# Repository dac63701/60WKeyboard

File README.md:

# Custom Keyboard Project

A wireless, 60% layout, hot swappable, custom keyboard designed with an nRF52840 in Kicad. This keyboard is meant to be as efficient as possible for longer battery life.

## Criteria
- Wireless
- 60% Layout
- RGB Lighting
- Good Battery Life
- Cherry MX Switch Form Factor
- Hotswap Switches

## Materials
- [ ] PCBs ([JLCPCB](https://jlcpcb.com))
- [ ] Solder Stencil ([JLCPCB](https://jlcpcb.com))
- [x] Solder Paste ([Amazon](https://www.amazon.com/gp/product/B0BLSJQPR6/ref=ox_sc_act_title_7?smid=A1NSYQXYRWRLYY&psc=1))
- [x] Flux ([Amazon](https://www.amazon.com/gp/product/B08KJRCYRH/ref=ox_sc_act_title_8?smid=A2GPLZGUK8NBW5&psc=1))
- [x] Lead-Free Solder ([Amazon](https://www.amazon.com/gp/product/B07Q167J98/ref=ewc_pr_img_4?smid=A2SCLCWYE2XLX3&psc=1))
- [x] Solder Wick ([Amazon](https://www.amazon.com/gp/product/B094GZ6CPZ/ref=ox_sc_act_title_11?smid=ATC1HM24MD6HA&psc=1))
- [x] Solder Tip Tinner ([Amazon](https://www.amazon.com/gp/product/B00NS4J6BY/ref=ewc_pr_img_1?smid=A614WYM65K035&psc=1))
- [x] Switches ([Gateron Milky Yellows](https://www.amazon.com/gp/product/B0BBPD1W9W/ref=ox_sc_act_title_13?smid=A3L9NMSYTD5SO9&psc=1))
- [ ] Hot Swap Sockets ([Amazon](https://www.amazon.com/gp/product/B0B4W9YMGM/ref=ox_sc_act_title_14?smid=A1G6HFHDKP9H5J&psc=1))
- [ ] Stabilizers ([Amazon](https://www.amazon.com/gp/product/B0CN36LV22/ref=ox_sc_act_title_12?smid=A1G6HFHDKP9H5J&psc=1))
- [x] Keycaps (Aliexpress)
- [ ] Case (3d Printed)

## Electronic Components ([Digikey](https://www.digikey.com/))
- Main MCU - [nRF52840](https://www.nordicsemi.com/Products/nRF52840)
- PMIC - [nPM1300](https://www.nordicsemi.com/Products/nPM1300)
- RGB LEDs - [SK6812mini-e](https://www.aliexpress.us/item/3256809003632879.html?spm=a2g0o.order_list.order_list_main.5.75471802QNYOMN&gatewayAdapt=glo2usa)
- Supporting Components...

## Tools
- [x] Adjustable Temperature Soldering Iron ([8786D](https://www.amazon.com/gp/product/B0BXN5NXFQ/ref=ox_sc_act_title_6?smid=A1YPRZ9PDHRQA5&psc=1))
- [x] Hot Air Station ([8786D](https://www.amazon.com/gp/product/B0BXN5NXFQ/ref=ox_sc_act_title_6?smid=A1YPRZ9PDHRQA5&psc=1))
- [x] Hot Plate (Amazon)
- [x] Fume Extractor ([Kotto](https://www.amazon.com/gp/product/B07VWDN29F/ref=ox_sc_act_title_2?smid=A38V7SOCF2OM8H&psc=1))
- [x] Digital Microscope ([AD246S-M](https://www.amazon.com/gp/product/B09VPPS96M/ref=ox_sc_act_title_5?smid=A2YDP7W2SGBPL2&psc=1))
- [ ] Tweezers (Amazon)
- [ ] Helping Hands ([Amazon](https://www.amazon.com/gp/product/B0BHHVP467/ref=ox_sc_act_title_10?smid=A3FKADQL4BXVZ2&psc=1))
- [ ] Soldering Iron Brass Sponge ([Amazon](https://www.amazon.com/gp/product/B08FQBS97L/ref=ox_sc_act_title_9?smid=ATVPDKIKX0DER&psc=1))
- [x] 3d Printer

## Steps
1. [x] Select Components
2. [x] Design Schematic
3. [x] Design PCB
4. [ ] Order PCB and Stencil
5. [ ] Order Electronic Components
6. [x] Acquire the necessary tools
7. [ ] Assemble boards
8. [ ] Test and validate

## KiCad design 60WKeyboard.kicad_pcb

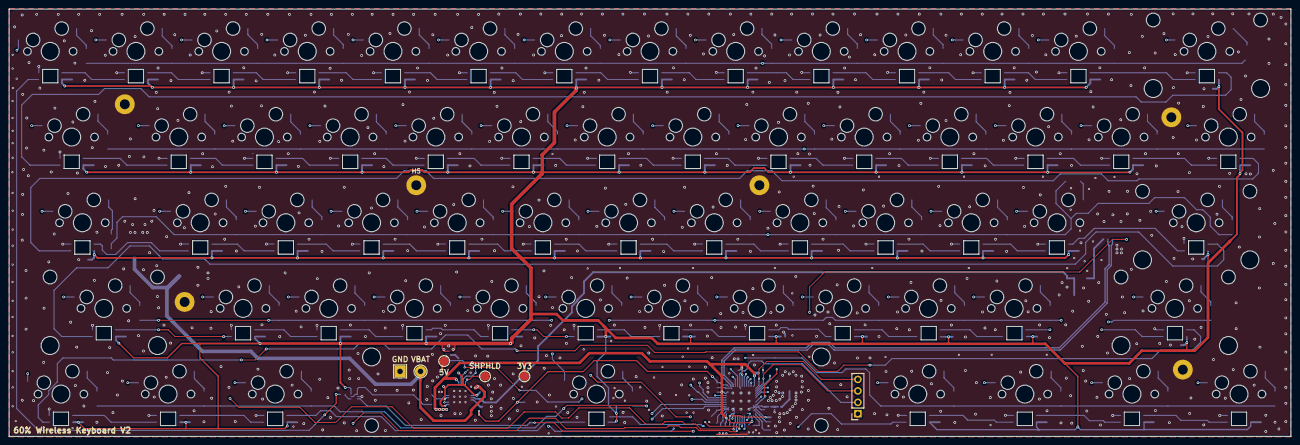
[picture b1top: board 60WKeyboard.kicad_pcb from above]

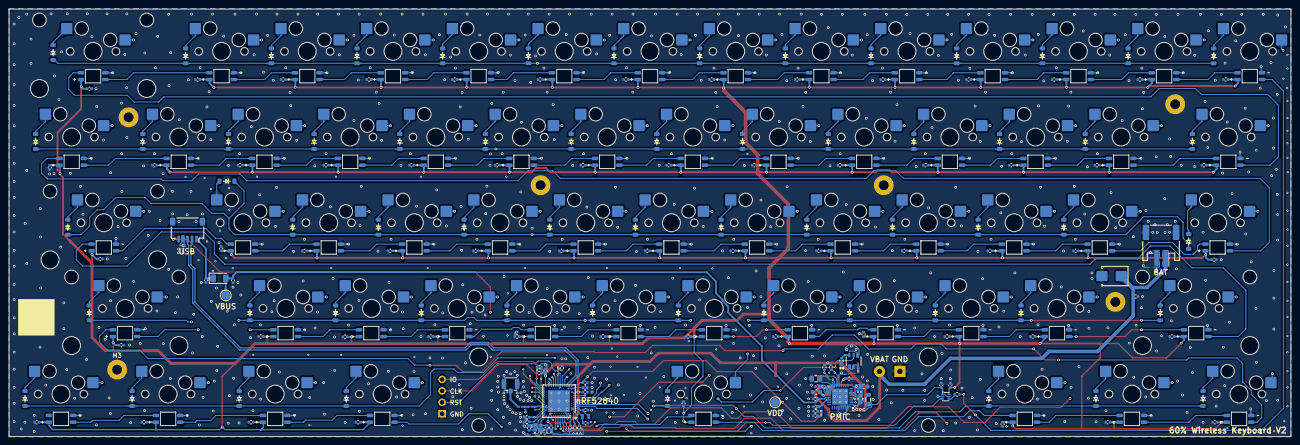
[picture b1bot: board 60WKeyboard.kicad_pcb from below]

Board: 4 copper layers, 285.0 x 95.0 mm, 310 parts (299 on the bottom side), 174 nets.

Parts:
3V3: USB_VBUS; TestPoint_Pad_D2.0mm
5V: 5V; TestPoint_Pad_D2.0mm
C1, C6, C8, C10, C13, C14, C30, C31, C32, C33, C34, C35, C36, C37, C38, C39, C40, C41, C42, C43, C44, C45, C46, C47, C48, C49, C50, C51, C52, C53, C54, C55, C56, C57, C58, C59, C60, C61, C62, C63, C64, C65, C66, C67, C68, C69, C70, C71, C72, C73, C74, C75, C76, C77, C78, C79, C80, C81, C82, C83, C84, C85, C86, C87, C88, C89, C90, C91, C92, C93: 100nF; C_0402_1005Metric
C2, C3, C5: 4.7uF; C_0402_1005Metric
C4, C11, C15: 1uF; C_0402_1005Metric
C7: DNP; C_0402_1005Metric
C9: 100pF; C_0402_1005Metric
C12, C17, C18, C19: 8pF; C_0402_1005Metric
C16: 2.2uF; C_0402_1005Metric
C20, C21, C22: 10uF; C_0603_1608Metric
C23, C24, C25: 3.3uF; C_0402_1005Metric
C26: 1pF; C_0201_0603Metric
C27, C29: 0.1uF; C_0402_1005Metric
C28: 1.2pF; C_0201_0603Metric
D1: D_TVS; D_SMB
D2, D3, D4, D5, D6, D7, D8, D9, D10, D11, D12, D13, D14, D15, D16, D17, D18, D19, D20, D21, D22, D23, D24, D25, D26, D27, D28, D29, D30, D31, D32, D33, D34, D35, D36, D37, D38, D39, D40, D41, D42, D43, D44, D45, D46, D47, D48, D49, D50, D51, D52, D53, D54, D55, D56, D57, D58, D59, D60, D61, D62: Diode; Diode_SOD-123
FB1: 300R; D_1206_3216Metric
GND: GND; TestPoint_THTPad_2.5x2.5mm_Drill1.2mm
H1, H2, H3, H4, H5, H6: MountingHole_Pad; MountingHole_2.2mm_M2_Pad
J1: Conn_02x01_MountingPin; JST_PH_S2B-PH-SM4-TB_1x02-1MP_P2.00mm_Horizontal
J2: Conn_01x04_Socket; PinSocket_1x04_P2.54mm_Vertical
J4: Conn_01x05_MountingPin; JST_SH_SM05B-SRSS-TB_1x05-1MP_P1.00mm_Horizontal
J5: Conn_Coaxial; U.FL_Hirose_U.FL-R-SMT-1_Vertical
L1: 2.2uH; L_0805_2012Metric
L2: 4.7nH; L_0201_0603Metric
L3: 2.2nH; L_0201_0603Metric
LED1, LED2, LED3, LED4, LED5, LED6, LED7, LED8, LED9, LED10, LED11, LED12, LED13, LED14, LED15, LED16, LED17, LED18, LED19, LED20, LED21, LED22, LED23, LED24, LED25, LED26, LED27, LED28, LED29, LED30, LED31, LED32, LED33, LED34, LED35, LED36, LED37, LED38, LED39, LED40, LED41, LED42, LED43, LED44, LED45, LED46, LED47, LED48, LED49, LED50, LED51, LED52, LED53, LED54, LED55, LED56, LED57, LED58, LED59, LED60, LED61: SK6812-E; LED_SK6812-E
MOSFET1: SI3865DDV-T1-GE3; TSOP6_MO-193C_VIS
PMIC: NPM1300-QEAA-R; QFN50P500X500X90-33N
R1: 250k; R_0805_2012Metric
R2, R3, R6: 10k; R_0402_1005Metric
R5: 300; R_0402_1005Metric
R7: 100k; R_0402_1005Metric
S1, S6, S7, S8, S10, S11, S12, S13, S15, S16, S17, S18, S19, S20, S21, S22, S23, S24, S25, S26, S27, S28, S29, S30, S32, S33, S34, S35, S36, S37, S38, S39, S40, S41, S42, S43, S44, S45, S46, S47, S49, S50, S51, S52, S54, S55: Keyswitch; MX-Hotswap-1U
S2, S58: Keyswitch; MX-Hotswap-1.5U
S3: Keyswitch; MX-Hotswap-1.75U
S4, S59: Keyswitch; MX-Hotswap-2.25U
S5, S9, S14, S48, S53, S56, S61: Keyswitch; MX-Hotswap-1.25U
S31: Keyswitch; MX-Hotswap-6.25U-ReversedStabilizers
S57: Keyswitch; MX-Hotswap-2U
S60: Keyswitch; MX-Hotswap-2.75U
SHPHLD: VBUSOUT; TestPoint_Pad_D2.0mm
U1: nRF52840; Nordic_AQFN-73-1EP_7x7mm_P0.5mm
U2: TXB0101DRL; SOT-563
VBAT: +BATT; TestPoint_THTPad_D2.5mm_Drill1.2mm
VBUS: USB_VBUS; TestPoint_Pad_D2.0mm
VDD: VBUSOUT; TestPoint_Pad_D2.0mm
Y1: ABM11W-32.0000MHZ-7-D1X-T3; ABM11W300000MHZ4B1UT3
Y2: ECS-.327-7-12-TR; XTAL_ECS-.327-7-12-TR

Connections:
+3V3: 3V3.1 (1_1), C2.1, C4.2, C6.1, C8.1, C10.1, C14.1, C22.1, C86.2, L1.1, PMIC.12 (VDDIO), PMIC.32 (VOUT2), R2.2, R3.2, R6.1, U1.A22 (VDD), U1.AD14 (VDD), U1.AD23 (VDD), U1.B1 (VDD), U1.W1 (VDD), U1.Y2 (VDDH), U2.1 (V_{CCA}), U2.5 (OE)
+5V: 5V.1 (1_1), C20.1, C21.1, C30.1, C31.1, C33.1, C34.1, C35.1, C36.1, C37.1, C38.1, C39.1, C40.1, C41.1, C42.1, C43.1, C44.1, C45.1, C46.1, C47.1, C48.1, C49.1, C50.1, C51.1, C52.1, C53.1, C54.1, C55.1, C56.1, C57.1, C58.1, C59.1, C60.1, C61.1, C62.1, C63.1, C64.1, C65.1, C66.1, C67.1, C68.1, C69.1, C70.1, C71.1, C72.1, C73.1, C74.1, C75.1, C76.1, C77.1, C78.1, C79.1, C80.1, C81.1, C82.1, C83.1, C84.1, C85.1, C87.1, C88.1, C89.1, C90.1, C91.1, C92.1, C93.1, LED1.1 (VDD), LED2.1 (VDD), LED3.1 (VDD), LED4.1 (VDD), LED5.1 (VDD), LED6.1 (VDD), LED7.1 (VDD), LED8.1 (VDD), LED9.1 (VDD), LED10.1 (VDD), LED11.1 (VDD), LED12.1 (VDD), LED13.1 (VDD), LED14.1 (VDD), LED15.1 (VDD), LED16.1 (VDD), LED17.1 (VDD), LED18.1 (VDD), LED19.1 (VDD), LED20.1 (VDD), LED21.1 (VDD), LED22.1 (VDD), LED23.1 (VDD), LED24.1 (VDD), LED25.1 (VDD), LED26.1 (VDD), LED27.1 (VDD), LED28.1 (VDD), LED29.1 (VDD), LED30.1 (VDD), LED31.1 (VDD), LED32.1 (VDD), LED33.1 (VDD), LED34.1 (VDD), LED35.1 (VDD), LED36.1 (VDD), LED37.1 (VDD), LED38.1 (VDD), LED39.1 (VDD), LED40.1 (VDD), LED41.1 (VDD), LED42.1 (VDD), LED43.1 (VDD), LED44.1 (VDD), LED45.1 (VDD), LED46.1 (VDD), LED47.1 (VDD), LED48.1 (VDD), LED49.1 (VDD), LED50.1 (VDD), LED51.1 (VDD), LED52.1 (VDD), LED53.1 (VDD), LED54.1 (VDD), LED55.1 (VDD), LED56.1 (VDD), LED57.1 (VDD), LED58.1 (VDD), LED59.1 (VDD), LED60.1 (VDD), LED61.1 (VDD), MOSFET1.1 (R2), MOSFET1.2 (D2), MOSFET1.3 (D2), MOSFET1.4 (S2), PMIC.1 (VOUT1), PMIC.4 (PVDD), PMIC.20 (VSYS), R7.2, U2.6 (V_{CCB})
+BATT: C13.1, C16.2, D1.1 (A1), J1.1, PMIC.19 (VBAT), VBAT.1 (1_1)
/ANT: C26.1, L2.1, U1.H23 (ANT)
/COL_0: S1.1, S2.1, S3.1, S4.1, S5.1, U1.A10 (AIN5/P0.29)
/COL_1: S6.1, S7.1, S8.1, S9.1, U1.A8 (AIN7/P0.31)
/COL_2: S10.1, S11.1, S12.1, S13.1, S14.1, U1.A14 (P1.15)
/COL_3: S15.1, S16.1, S17.1, S18.1, U1.A12 (AIN0/P0.02)
/COL_4: S19.1, S20.1, S21.1, S22.1, U1.A20 (P1.10)
/COL_5: S23.1, S24.1, S25.1, S26.1, U1.B19 (P1.11)
/COL_6: S27.1, S28.1, S29.1, S30.1, S31.1, U1.U1 (TRACEDATA1/P0.12)
/COL_7: S32.1, S33.1, S34.1, S35.1, U1.N1 (P0.08)
/COL_8: S36.1, S37.1, S38.1, S39.1, U1.R1 (TRACEDATA3/P1.09)
/COL_9: S40.1, S41.1, S42.1, S43.1, U1.AD22 (TRACEDATA0/P1.00)
/COL_10: S44.1, S45.1, S46.1, S47.1, S48.1, U1.U24 (P1.04)
/COL_11: S49.1, S50.1, S51.1, S52.1, S53.1, U1.W24 (P1.02)
/COL_12: S54.1, S55.1, S56.1, U1.J24 (NFC2/P0.10)
/COL_13: S57.1, S58.1, S59.1, S60.1, S61.1, U1.R24 (P1.06)
/C_VBUS: C27.1, FB1.1, J4.1
/DEC 1: C1.2, U1.C1 (DEC1)
/DEC 3: C9.1, U1.D23 (DEC3)
/DEC 4 6: C7.1, C11.2, U1.B5 (DEC4), U1.E24 (DEC6)
/DECUSB: C5.1, U1.AC5 (DECUSB)
/LEDs/RGB_DIN_5V: LED1.4 (DIN), R5.1
/PWR_SW: C32.2, J4.5, R6.2, U1.L24 (NFC1/P0.09)
/RESET: J2.2, U1.AC13 (P0.18/~RESET), U1.AD12 (P0.17)
/RF: J5.1 (In), L3.2
/RGB_DIN_3V3: U1.A16 (P1.13), U2.3 (A)
/RGB_POWER: MOSFET1.5 (ON/OFF), U1.L1 (P0.06)
/ROW_0: D2.1 (K), D7.1 (K), D11.1 (K), D16.1 (K), D20.1 (K), D24.1 (K), D28.1 (K), D33.1 (K), D37.1 (K), D41.1 (K), D45.1 (K), D50.1 (K), D55.1 (K), D58.1 (K), U1.AD20 (P0.24)
/ROW_1: D3.1 (K), D8.1 (K), D12.1 (K), D17.1 (K), D21.1 (K), D25.1 (K), D29.1 (K), D34.1 (K), D38.1 (K), D42.1 (K), D46.1 (K), D51.1 (K), D56.1 (K), D59.1 (K), U1.AD18 (P0.22)
/ROW_2: D4.1 (K), D9.1 (K), D13.1 (K), D18.1 (K), D22.1 (K), D26.1 (K), D30.1 (K), D35.1 (K), D39.1 (K), D43.1 (K), D47.1 (K), D52.1 (K), D60.1 (K), U1.AD16 (P0.20)
/ROW_3: D5.1 (K), D14.1 (K), D19.1 (K), D23.1 (K), D27.1 (K), D31.1 (K), D36.1 (K), D40.1 (K), D44.1 (K), D48.1 (K), D53.1 (K), D61.1 (K), U1.AD10 (P0.15)
/ROW_4: D6.1 (K), D10.1 (K), D15.1 (K), D32.1 (K), D49.1 (K), D54.1 (K), D57.1 (K), D62.1 (K), U1.AD8 (P0.13)
/SCL: PMIC.14 (SCL), R2.1, U1.G1 (P0.26)
/SDA: PMIC.13 (SDA), R3.1, U1.J1 (AIN2/P0.04)
/SHPHLD: PMIC.15 (SHPHLD), SHPHLD.1 (1_1)
/SWDCLK: J2.3, U1.AA24 (SWDCLK)
/SWDIO: J2.4, U1.AC24 (SWDIO)
/USB_DN: J4.2, U1.AD4 (D-)
/USB_DP: J4.3, U1.AD6 (D+)
/XC1: C12.1, U1.B24 (XC1), Y1.1 (X1)
/XC2: C17.1, U1.A23 (XC2), Y1.3 (X2)
/XL1: C18.2, U1.D2 (XL1/P0.00), Y2.1
/XL2: C19.2, U1.F2 (XL2/P0.01), Y2.2
GND: C1.1, C2.2, C3.2, C4.1, C5.2, C6.2, C7.2, C8.2, C9.2, C10.2, C11.1, C12.2, C13.2, C14.2, C15.2, C16.1, C17.2, C18.1, C19.1, C20.2, C21.2, C22.2, C23.2, C24.2, C25.2, C26.2, C27.2, C28.2, C29.2, C30.2, C31.2, C32.1, C33.2, C34.2, C35.2, C36.2, C37.2, C38.2, C39.2, C40.2, C41.2, C42.2, C43.2, C44.2, C45.2, C46.2, C47.2, C48.2, C49.2, C50.2, C51.2, C52.2, C53.2, C54.2, C55.2, C56.2, C57.2, C58.2, C59.2, C60.2, C61.2, C62.2, C63.2, C64.2, C65.2, C66.2, C67.2, C68.2, C69.2, C70.2, C71.2, C72.2, C73.2, C74.2, C75.2, C76.2, C77.2, C78.2, C79.2, C80.2, C81.2, C82.2, C83.2, C84.2, C85.2, C86.1, C87.2, C88.2, C89.2, C90.2, C91.2, C92.2, C93.2, D1.2 (A2), GND.1 (1_1), H1.1 (1_1), H2.1 (1_1), H3.1 (1_1), H4.1 (1_1), H5.1 (1_1), H6.1 (1_1), J1.2, J1.MP (MountPin), J2.1, J4.4, J4.MP (MountPin), J5.2 (Ext), LED1.3 (GND), LED2.3 (GND), LED3.3 (GND), LED4.3 (GND), LED5.3 (GND), LED6.3 (GND), LED7.3 (GND), LED8.3 (GND), LED9.3 (GND), LED10.3 (GND), LED11.3 (GND), LED12.3 (GND), LED13.3 (GND), LED14.3 (GND), LED15.3 (GND), LED16.3 (GND), LED17.3 (GND), LED18.3 (GND), LED19.3 (GND), LED20.3 (GND), LED21.3 (GND), LED22.3 (GND), LED23.3 (GND), LED24.3 (GND), LED25.3 (GND), LED26.3 (GND), LED27.3 (GND), LED28.3 (GND), LED29.3 (GND), LED30.3 (GND), LED31.3 (GND), LED32.3 (GND), LED33.3 (GND), LED34.3 (GND), LED35.3 (GND), LED36.3 (GND), LED37.3 (GND), LED38.3 (GND), LED39.3 (GND), LED40.3 (GND), LED41.3 (GND), LED42.3 (GND), LED43.3 (GND), LED44.3 (GND), LED45.3 (GND), LED46.3 (GND), LED47.3 (GND), LED48.3 (GND), LED49.3 (GND), LED50.3 (GND), LED51.3 (GND), LED52.3 (GND), LED53.3 (GND), LED54.3 (GND), LED55.3 (GND), LED56.3 (GND), LED57.3 (GND), LED58.3 (GND), LED59.3 (GND), LED60.3 (GND), LED61.3 (GND), PMIC.2 (PVSS1), PMIC.6 (PVSS2), PMIC.17 (VSET1), PMIC.18 (NTC), PMIC.28 (LSIN1/VINLDO1), PMIC.29 (LSOUT1/VOUTLDO1), PMIC.30 (LSIN2/VINLDO2), PMIC.31 (LSOUT2/VOUTLDO2), PMIC.33 (AVSS), R1.1, U1.B7 (VSS), U1.EP (VSS), U1.F23 (VSS_PA), U2.2 (GND), Y1.2 (GND_1), Y1.4 (GND_2)
unnamed: C28.1, L2.2, L3.1
unnamed: D2.2 (A), S1.2
unnamed: D3.2 (A), S2.2
unnamed: D4.2 (A), S3.2
unnamed: D5.2 (A), S4.2
unnamed: D6.2 (A), S5.2
unnamed: D7.2 (A), S6.2
unnamed: D8.2 (A), S7.2
unnamed: D9.2 (A), S8.2
unnamed: D10.2 (A), S9.2
unnamed: D11.2 (A), S10.2
unnamed: D12.2 (A), S11.2
unnamed: D13.2 (A), S12.2
unnamed: D14.2 (A), S13.2
unnamed: D15.2 (A), S14.2
unnamed: D16.2 (A), S15.2
unnamed: D17.2 (A), S16.2
unnamed: D18.2 (A), S17.2
unnamed: D19.2 (A), S18.2
unnamed: D20.2 (A), S19.2
unnamed: D21.2 (A), S20.2
unnamed: D22.2 (A), S21.2
unnamed: D23.2 (A), S22.2
unnamed: D24.2 (A), S23.2
unnamed: D25.2 (A), S24.2
unnamed: D26.2 (A), S25.2
unnamed: D27.2 (A), S26.2
unnamed: D28.2 (A), S27.2
unnamed: D29.2 (A), S28.2
unnamed: D30.2 (A), S29.2
unnamed: D31.2 (A), S30.2
unnamed: D32.2 (A), S31.2
unnamed: D33.2 (A), S32.2
unnamed: D34.2 (A), S33.2
unnamed: D35.2 (A), S34.2
unnamed: D36.2 (A), S35.2
unnamed: D37.2 (A), S36.2
unnamed: D38.2 (A), S37.2
unnamed: D39.2 (A), S38.2
unnamed: D40.2 (A), S39.2
unnamed: D41.2 (A), S40.2
unnamed: D42.2 (A), S41.2
unnamed: D43.2 (A), S42.2
unnamed: D44.2 (A), S43.2
unnamed: D45.2 (A), S44.2
unnamed: D46.2 (A), S45.2
unnamed: D47.2 (A), S46.2
unnamed: D48.2 (A), S47.2
unnamed: D49.2 (A), S48.2
unnamed: D50.2 (A), S49.2
unnamed: D51.2 (A), S50.2
unnamed: D52.2 (A), S51.2
unnamed: D53.2 (A), S52.2
unnamed: D54.2 (A), S53.2
unnamed: D55.2 (A), S54.2
unnamed: D56.2 (A), S55.2
unnamed: D57.2 (A), S56.2
unnamed: D58.2 (A), S57.2
unnamed: D59.2 (A), S58.2
unnamed: D60.2 (A), S59.2
unnamed: D61.2 (A), S60.2
unnamed: D62.2 (A), S61.2
unnamed: LED1.2 (DOUT), LED6.4 (DIN)
unnamed: LED2.4 (DIN), LED60.2 (DOUT)
unnamed: LED2.2 (DOUT), LED7.4 (DIN)
unnamed: LED3.4 (DIN), LED61.2 (DOUT)
unnamed: LED3.2 (DOUT), LED8.4 (DIN)
unnamed: LED4.4 (DIN), LED59.2 (DOUT)
unnamed: LED4.2 (DOUT), LED9.4 (DIN)
unnamed: LED5.4 (DIN), LED56.2 (DOUT)
unnamed: LED5.2 (DOUT), LED10.4 (DIN)
unnamed: LED10.2 (DOUT), LED15.4 (DIN)
unnamed: LED6.2 (DOUT), LED11.4 (DIN)
unnamed: LED11.2 (DOUT), LED16.4 (DIN)
unnamed: LED7.2 (DOUT), LED12.4 (DIN)
unnamed: LED12.2 (DOUT), LED17.4 (DIN)
unnamed: LED8.2 (DOUT), LED13.4 (DIN)
unnamed: LED13.2 (DOUT), LED18.4 (DIN)
unnamed: LED9.2 (DOUT), LED14.4 (DIN)
unnamed: LED14.2 (DOUT), LED19.4 (DIN)
unnamed: LED15.2 (DOUT), LED20.4 (DIN)
unnamed: LED16.2 (DOUT), LED21.4 (DIN)
unnamed: LED17.2 (DOUT), LED22.4 (DIN)
unnamed: LED18.2 (DOUT), LED23.4 (DIN)
unnamed: LED19.2 (DOUT), LED24.4 (DIN)
unnamed: LED20.2 (DOUT), LED25.4 (DIN)
unnamed: LED21.2 (DOUT), LED26.4 (DIN)
unnamed: LED22.2 (DOUT), LED27.4 (DIN)
unnamed: LED23.2 (DOUT), LED28.4 (DIN)
unnamed: LED24.2 (DOUT), LED29.4 (DIN)
unnamed: LED25.2 (DOUT), LED30.4 (DIN)
unnamed: LED26.2 (DOUT), LED31.4 (DIN)
unnamed: LED27.2 (DOUT), LED32.4 (DIN)
unnamed: LED28.2 (DOUT), LED33.4 (DIN)
unnamed: LED29.2 (DOUT), LED34.4 (DIN)
unnamed: LED30.2 (DOUT), LED35.4 (DIN)
unnamed: LED31.2 (DOUT), LED36.4 (DIN)
unnamed: LED32.2 (DOUT), LED37.4 (DIN)
unnamed: LED33.2 (DOUT), LED38.4 (DIN)
unnamed: LED34.2 (DOUT), LED39.4 (DIN)
unnamed: LED35.2 (DOUT), LED40.4 (DIN)
unnamed: LED36.2 (DOUT), LED41.4 (DIN)
unnamed: LED37.2 (DOUT), LED42.4 (DIN)
unnamed: LED38.2 (DOUT), LED43.4 (DIN)
unnamed: LED39.2 (DOUT), LED44.4 (DIN)
unnamed: LED41.2 (DOUT), LED45.4 (DIN)
unnamed: LED42.2 (DOUT), LED46.4 (DIN)
unnamed: LED43.2 (DOUT), LED47.4 (DIN)
unnamed: LED44.2 (DOUT), LED48.4 (DIN)
unnamed: LED45.2 (DOUT), LED49.4 (DIN)
unnamed: LED46.2 (DOUT), LED50.4 (DIN)
unnamed: LED47.2 (DOUT), LED51.4 (DIN)
unnamed: LED48.2 (DOUT), LED52.4 (DIN)
unnamed: LED49.2 (DOUT), LED53.4 (DIN)
unnamed: LED50.2 (DOUT), LED54.4 (DIN)
unnamed: LED51.2 (DOUT), LED55.4 (DIN)
unnamed: LED52.2 (DOUT), LED56.4 (DIN)
unnamed: LED53.2 (DOUT), LED57.4 (DIN)
unnamed: LED54.2 (DOUT), LED58.4 (DIN)
unnamed: LED55.2 (DOUT), LED59.4 (DIN)
unnamed: LED57.2 (DOUT), LED60.4 (DIN)
unnamed: LED58.2 (DOUT), LED61.4 (DIN)
unnamed: MOSFET1.6 (R1,C1), R7.1
unnamed: L1.2, PMIC.5 (SW2)
unnamed: PMIC.16 (VSET2), R1.2
unnamed: R5.2, U2.4 (B)
VBUS: C15.1, C29.1, FB1.2, PMIC.21 (VBUS), VBUS.1 (1_1)
VDD: C3.1, C23.1, C24.1, C25.1, PMIC.22 (VBUSOUT), U1.AD2 (VBUS), VDD.1 (1_1)

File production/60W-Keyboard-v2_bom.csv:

Designator,Footprint,Quantity,Value,LCSC Part #
"3V3, VBUS",TestPoint_Pad_D2.0mm,2,USB_VBUS,
5V,TestPoint_Pad_D2.0mm,1,5V,
"C1, C10, C13, C14, C30, C31, C32, C33, C34, C35, C36, C37, C38, C39, C40, C41, C42, C43, C44, C45, C46, C47, C48, C49, C50, C51, C52, C53, C54, C55, C56, C57, C58, C59, C6, C60, C61, C62, C63, C64, C65, C66, C67, C68, C69, C70, C71, C72, C73, C74, C75, C76, C77, C78, C79, C8, C80, C81, C82, C83, C84, C85, C86, C87, C88, C89, C90, C91, C92, C93",0402,70,100nF,
"C11, C15, C4",0402,3,1uF,
"C12, C17, C18, C19",0402,4,8pF,
C16,0402,1,2.2uF,
"C2, C3, C5",0402,3,4.7uF,
"C20, C21, C22",0603,3,10uF,
"C23, C24, C25",0402,3,3.3uF,
C26,0201,1,1pF,
"C27, C29",0402,2,0.1uF,
C28,0201,1,1.2pF,
C9,0402,1,100pF,
D1,D_SMB,1,D_TVS,
"D10, D11, D12, D13, D14, D15, D16, D17, D18, D19, D2, D20, D21, D22, D23, D24, D25, D26, D27, D28, D29, D3, D30, D31, D32, D33, D34, D35, D36, D37, D38, D39, D4, D40, D41, D42, D43, D44, D45, D46, D47, D48, D49, D5, D50, D51, D52, D53, D54, D55, D56, D57, D58, D59, D6, D60, D61, D62, D7, D8, D9",Diode_SOD-123,61,Diode,
FB1,1206,1,300R,
J1,JST_PH_S2B-PH-SM4-TB_1x02-1MP_P2.00mm_Horizontal,1,Conn_02x01_MountingPin,
J2,PinSocket_1x04_P2.54mm_Vertical,1,Conn_01x04_Socket,
J4,JST_SH_SM05B-SRSS-TB_1x05-1MP_P1.00mm_Horizontal,1,Conn_01x05_MountingPin,
J5,U.FL_Hirose_U.FL-R-SMT-1_Vertical,1,Conn_Coaxial,
L1,0805,1,2.2uH,
L2,0201,1,4.7nH,
L3,0201,1,2.2nH,
"LED1, LED10, LED11, LED12, LED13, LED14, LED15, LED16, LED17, LED18, LED19, LED2, LED20, LED21, LED22, LED23, LED24, LED25, LED26, LED27, LED28, LED29, LED3, LED30, LED31, LED32, LED33, LED34, LED35, LED36, LED37, LED38, LED39, LED4, LED40, LED41, LED42, LED43, LED44, LED45, LED46, LED47, LED48, LED49, LED5, LED50, LED51, LED52, LED53, LED54, LED55, LED56, LED57, LED58, LED59, LED6, LED60, LED61, LED7, LED8, LED9",LED_SK6812-E,61,SK6812-E,
PMIC,QFN50P500X500X90-33N,1,NPM1300-QEAA-R,
Q1,SOT-23,1,DMG2301L,
R1,0805,1,250k,
"R2, R3, R4, R6",0402,4,10k,
R5,0402,1,300,
"S1, S10, S11, S12, S13, S15, S16, S17, S18, S19, S20, S21, S22, S23, S24, S25, S26, S27, S28, S29, S30, S32, S33, S34, S35, S36, S37, S38, S39, S40, S41, S42, S43, S44, S45, S46, S47, S49, S50, S51, S52, S54, S55, S6, S7, S8",MX-Hotswap-1U,46,Keyswitch,
"S14, S48, S5, S53, S56, S61, S9",MX-Hotswap-1.25U,7,Keyswitch,
"S2, S58",MX-Hotswap-1.5U,2,Keyswitch,
S3,MX-Hotswap-1.75U,1,Keyswitch,
S31,MX-Hotswap-6.25U-ReversedStabilizers,1,Keyswitch,
"S4, S59",MX-Hotswap-2.25U,2,Keyswitch,
S57,MX-Hotswap-2U,1,Keyswitch,
S60,MX-Hotswap-2.75U,1,Keyswitch,
"SHPHLD, VDD",TestPoint_Pad_D2.0mm,2,VBUSOUT,
U1,Nordic_AQFN-73-1EP_7x7mm_P0.5mm,1,nRF52840,
U2,SOT-563,1,TXB0101DRL,
Y1,ABM11W300000MHZ4B1UT3,1,ABM11W-32.0000MHZ-7-D1X-T3,
Y2,XTAL_ECS-.327-7-12-TR,1,ECS-.327-7-12-TR,

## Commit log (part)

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2025-07-03 v0.1-sch
    finished schematic
2025-07-06 work towards v0.2
    Complete rework of design from nrf52840 module to nrf54l15 SOC with custom design. Adding new PMIC - npm1300 and supporting components for better fit on board and power savings.
2025-07-07 initial v0.2 schematic
    Finished initial schematic. nPM1300 and nRF54l15 are wired up.
2025-07-08 created v0.2 pcb
    Started work on v0.2 pcb. Placed switches, LEDS, and Diodes. Working on MCU routing
2025-07-10 v0.2 in dev
    MCU change because im stupid and now I have to redo rf. Routed columns. Started routing USB port.
2025-07-10 testomg
    1212
2025-07-10 Revert "testomg"
    This reverts commit 211e228692b4c4c07afb065cb12b80aeb16a1983.
2025-07-12 work towards v0.2
    Finished updating schematic. Ported to PCB editor. Need to rethink encoder.
2025-07-12 Update README.md
    crossed off done items
2025-07-13 work on v0.2
    Moved USB port a bit to facilitate easier routing of the ESD protection. Connected all diodes to keys. Connected most LEDS together.
2025-07-17 work towards v0.2
    QFAA needs replacement with QIAA
2025-07-26 more work towards v0.2
2025-09-21 v0.3
    moving along
    everything on board
    need to wire chip and batt charger ic
    switch matrix mostly done
2025-09-22 v0.3
    mcu power traces done
    moving onto pmic
    then connect key matrix
    then done?
2025-09-23 v0.3
    finished npm1300 routing
    just columns and rows to go
    get review
    order
2025-09-24 v0.3
    done
    waiting for review
2025-10-12 v0.3
    finally finished
2025-10-16 final updates
2025-10-23 Check off completed materials and steps
    Updated the materials and steps sections to reflect completed tasks.
2025-10-30 Enhance README with image and project details
    Added a screenshot and improved project description.
2025-10-30 Fix image path in README.md
2025-10-30 added bom
2025-10-30 bom.csv location move
    its in the right location now
2025-11-09 Add RGB power control circuit and update PCB
    Introduced a new RGB power control circuit using a DMG2301L MOSFET and 10k resistor, connected to the /RGB_POWER net. Updated test point references, modified net assignments, and adjusted routing and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
2025-11-14 Add .gitignore and update keyboard backups
    Added .gitignore to exclude Keyboard-Examples directory. Removed old keyboard backup and added a new backup zip file.
2025-11-19 v0.3 complete
    everything fixed (vias are good now) fixed all the other stuff too
2025-11-19 updated review files
2025-11-22 Replace RF footprint and add U.FL connector
    Replaced the AMCA31-2R450G-S1F-T3 RF footprint with a CONMHF1-SMD-T U.FL connector at the RF output. Updated the S57 keyswitch footprint position. Also updated backup files and production outputs to 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
2025-11-22 Update KiCad project files and backup
    Removed autosave and lock files, updated project and schematic files, and renamed backup ZIP. Changed footprint property for connector in schematic and adjusted selection filter for footprints in pro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
2025-11-22 Update PCB plot parameters and review files
    Modified plot layer selection parameters in 60WKeyboard.kicad_pcb and updated all related review PDFs and backup ZIP to reflect the latest board changes.
2025-11-25 v0.4-routing done
    need to work on routing and fix it up but preliminary routing done
2025-11-30 v0.4 done
    updated everything
2025-11-30 v0.4 update
    more updates to pcb
2025-11-30 v0.4 update
    review files updated
2025-11-30 Remove KiCad lock files
    Deleted temporary lock files for the PCB and schematic to clean up the repository.
2025-11-30 Update checklist items in README
    Updated the checklist in the README to mark several items as completed.
2025-11-30 Change keyboard screenshot in README
    Updated the screenshot image in the README.
2025-11-30 Update PCB and production files for v0.4 release
    Replaced and added backup and production ZIP files for 60W Keyboard v0.4, updated BOM, designators, and positions CSVs, and modified the PCB and netlist files. Also fixed zone connection and region l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
